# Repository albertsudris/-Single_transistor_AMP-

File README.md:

# -Single_transistor_AMP-
# Single_Transistor_Amp
# Design-Rules

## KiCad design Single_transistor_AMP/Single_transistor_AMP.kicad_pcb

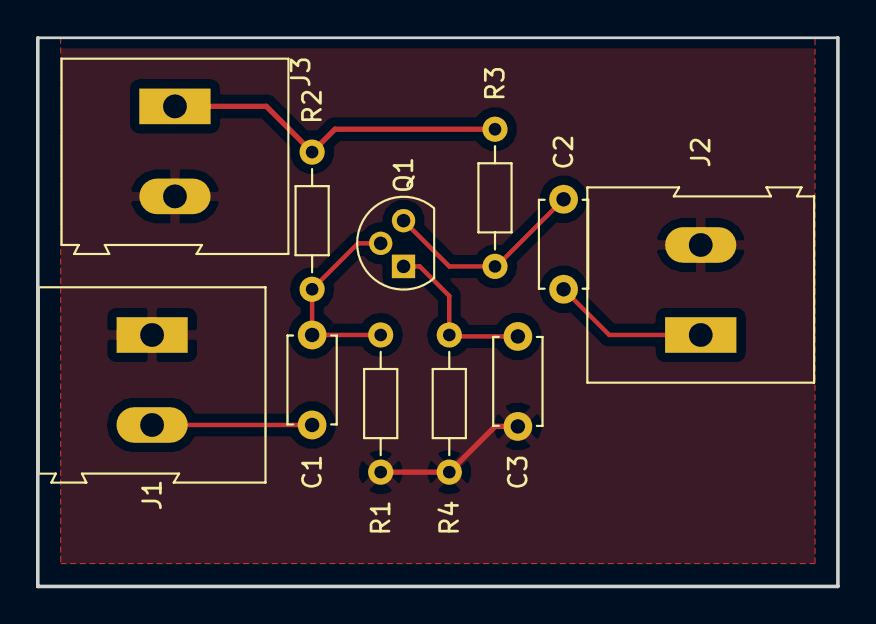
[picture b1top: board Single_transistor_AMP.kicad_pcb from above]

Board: 2 copper layers, 44.5 x 30.5 mm, 11 parts (0 on the bottom side), 7 nets.

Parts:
C1: 1uF; C_Disc_D4.7mm_W2.5mm_P5.00mm
C2: 4.7uF; C_Disc_D4.7mm_W2.5mm_P5.00mm
C3: 22uF; C_Disc_D4.7mm_W2.5mm_P5.00mm
J1, J2: Conn_01x02; TerminalBlock_Altech_AK300-2_P5.00mm
J3: Screw_Terminal_01x02; TerminalBlock_Altech_AK300-2_P5.00mm
Q1: 2N2219; TO-92L
R1, R4: 1K; R_Axial_DIN0204_L3.6mm_D1.6mm_P7.62mm_Horizontal
R2, R3: 4.7K; R_Axial_DIN0204_L3.6mm_D1.6mm_P7.62mm_Horizontal

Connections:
GND: C3.2, J1.1, J2.2, J3.2, R1.1, R4.1
unnamed: C1.1, Q1.2, R1.2, R2.2
unnamed: C1.2, J1.2
unnamed: C2.1, J2.1
unnamed: C2.2, Q1.3, R3.2
unnamed: C3.1, Q1.1, R4.2
VCC: J3.1, R2.1, R3.1

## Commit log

2019-04-08 first commiRt
2019-04-08 first commiRtF
2019-04-25 first commiRtdfF
2019-04-25 first commiRtdfFd
